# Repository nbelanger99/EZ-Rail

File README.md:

# EZ-Rail

EZ-rail is a small 3.3v & 5v 1A power supply that runs off of a 9v battery. It's indended for use testing & prototpying digital electronics when conventional lab power supply isn't available. The board itself is the size of a 9v battery & sits on top of a battery holder. All components are through-hole, making it a great beginner soldering project. 

<br>

<br>

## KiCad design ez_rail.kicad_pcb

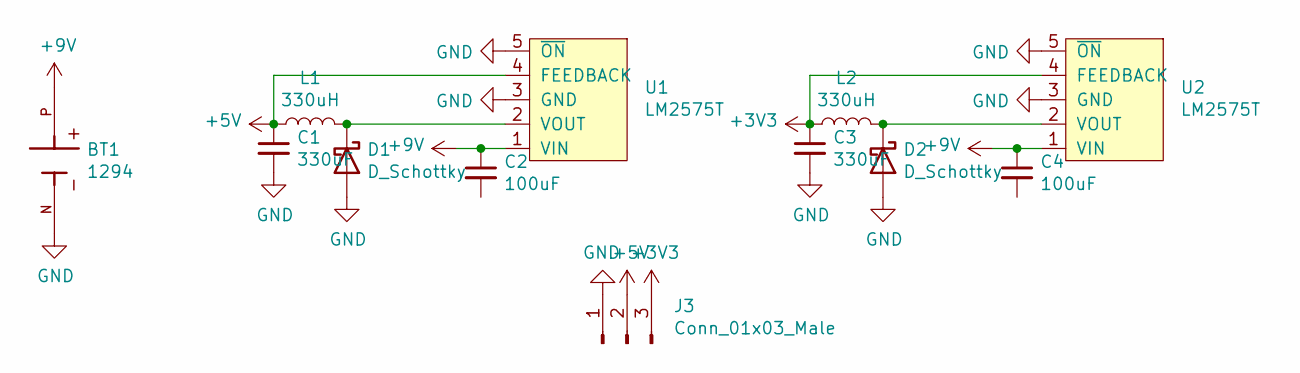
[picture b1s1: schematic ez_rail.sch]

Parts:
BT1: 1294; BAT_1294; PARTREV C
C1, C3: 330uF; CP_Radial_D10.0mm_P5.00mm
C2, C4: 100uF; CP_Radial_D6.3mm_P2.50mm
D1, D2: D_Schottky; D_DO-41_SOD81_P10.16mm_Horizontal
J3: Conn_01x03_Male; PinHeader_1x03_P2.54mm_Vertical
L1, L2: 330uH; L_Radial_D10.5mm_P5.00mm_Abacron_AISR-01
U1, U2: LM2575T; TO-220-5_Vertical

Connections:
+3V3: C3.1, J3.3, L2.1, U2.4 (FEEDBACK)
+5V: C1.1, J3.2, L1.1, U1.4 (FEEDBACK)
+9V: BT1.P, C2.1, C4.1, U1.1 (VIN), U2.1 (VIN)
GND: BT1.N, C1.2, C3.2, D1.2 (A), D2.2 (A), J3.1, U1.3 (GND), U1.5 (~ON), U2.3 (GND), U2.5 (~ON)
unnamed: D1.1 (K), L1.2, U1.2 (VOUT)
unnamed: D2.1 (K), L2.2, U2.2 (VOUT)

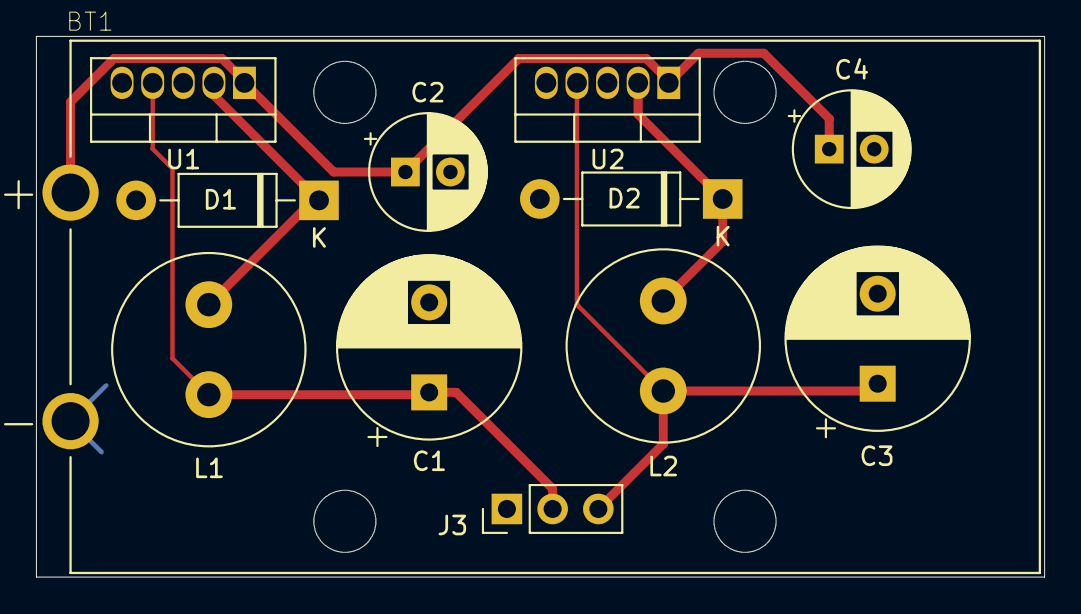
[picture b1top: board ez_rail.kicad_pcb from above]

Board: 2 copper layers, 56.0 x 30.0 mm, 12 parts (0 on the bottom side), 6 nets.

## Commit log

2021-02-13 Finishing layout, adding gitignore, removing cache file
    Adding media & readme
